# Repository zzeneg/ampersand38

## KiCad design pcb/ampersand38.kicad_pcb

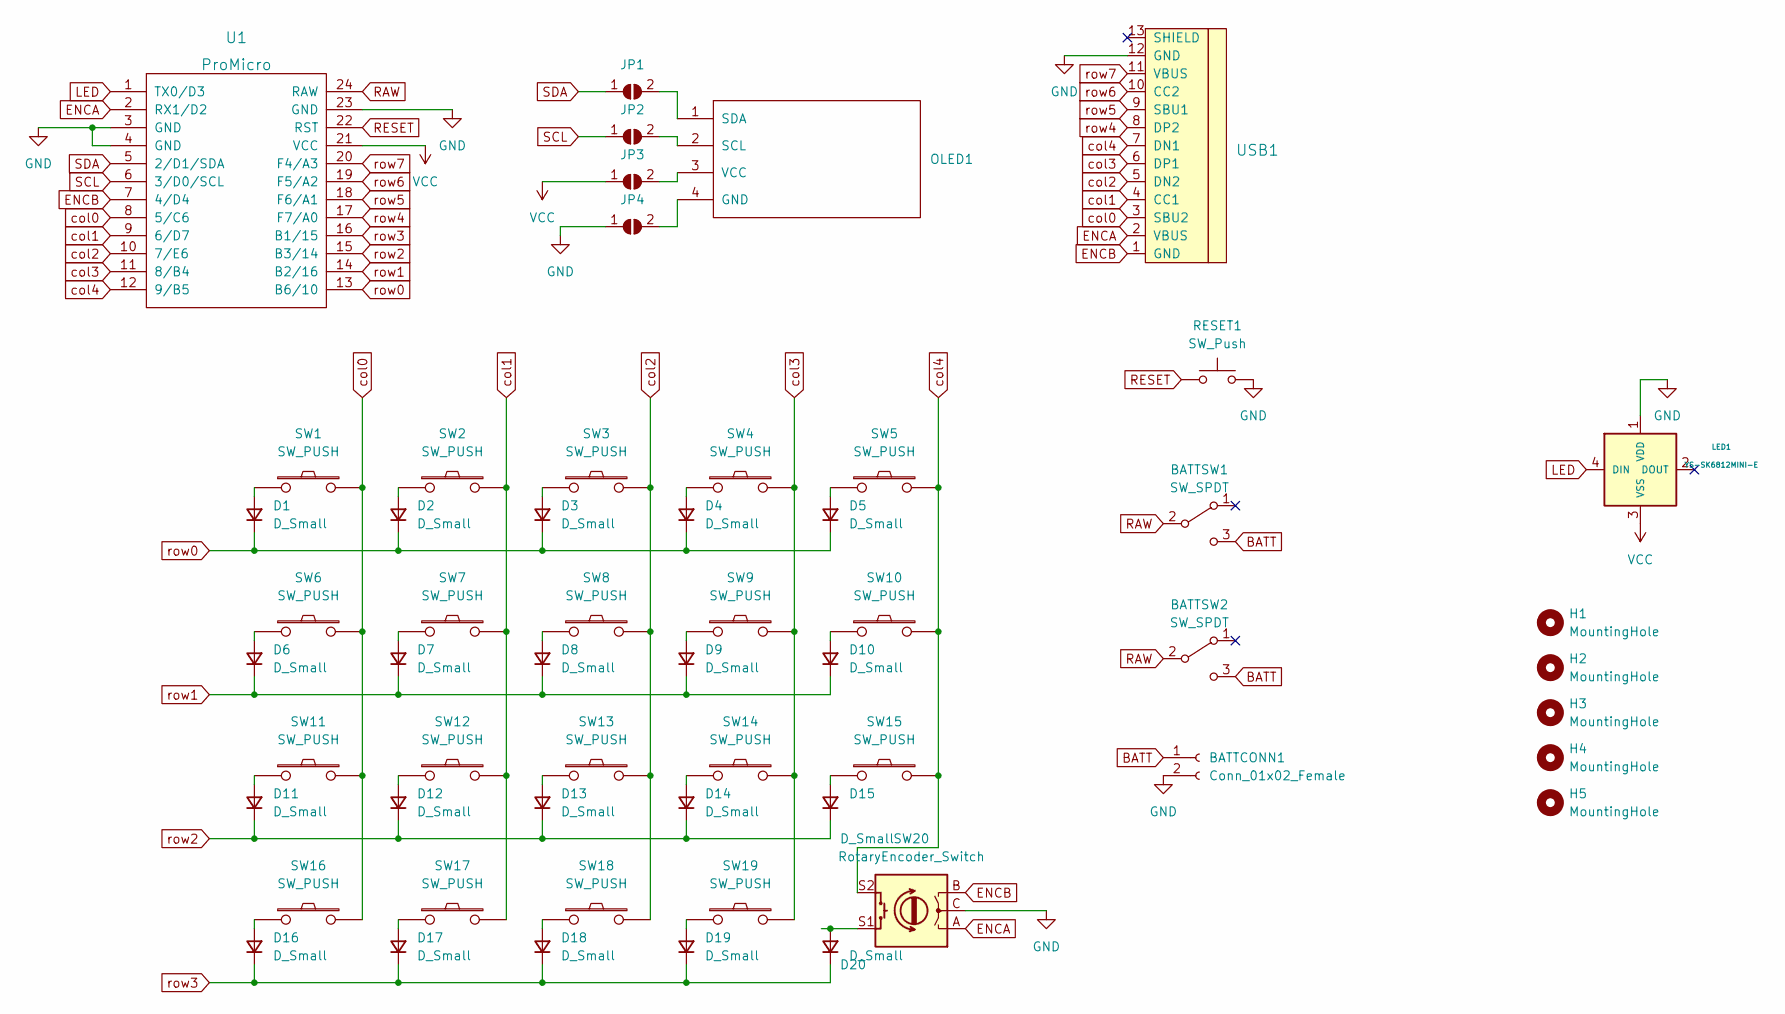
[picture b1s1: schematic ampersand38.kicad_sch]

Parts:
BATTCONN1: Conn_01x02_Female; JST_XH_S2B-XH-A_1x02_P2.50mm_Horizontal
BATTSW1, BATTSW2: SW_SPDT; SW_SPDT_PCM12
D1, D2, D3, D4, D5, D6, D7, D8, D9, D10, D11, D12, D13, D14, D15, D16, D17, D18, D19, D20: D_Small; D_SOD123
H1, H2, H3, H4, H5: MountingHole
JP1, JP2, JP3, JP4: SolderJumper_2_Open; SolderJumper-2_P1.3mm_Open_TrianglePad1.0x1.5mm
LED1: YS-SK6812MINI-E; SK6812-MINI-E
OLED1: OLED; OLED_v2
RESET1: SW_Push; ResetSW
SW1, SW2, SW3, SW4, SW5, SW6, SW7, SW8, SW9, SW10, SW11, SW12, SW13, SW14, SW15, SW16, SW17, SW18: SW_PUSH; CherryMX_Hotswap
SW19: SW_PUSH; CherryMX_Hotswap_1.5
SW20: RotaryEncoder_Switch; RotaryEncoder_EC11-no-legs
U1: ProMicro
USB1: HRO-TYPE-C-31-M-12

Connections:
BATT: BATTCONN1.1, BATTSW1.3 (C), BATTSW2.3 (C)
ENCA: SW20.A, U1.2 (RX1/D2), USB1.2 (VBUS)
ENCB: SW20.B, U1.7 (4/D4), USB1.1 (GND)
GND: BATTCONN1.2, JP4.1 (A), LED1.1 (VDD), RESET1.2, SW20.C, U1.3 (GND), U1.4 (GND), U1.23 (GND), USB1.12 (GND)
LED: LED1.4 (DIN), U1.1 (TX0/D3)
unnamed: D1.2 (A), SW1.1
unnamed: D2.2 (A), SW2.1
unnamed: D3.2 (A), SW3.1
unnamed: D4.2 (A), SW4.1
unnamed: D5.2 (A), SW5.1
unnamed: D6.2 (A), SW6.1
unnamed: D7.2 (A), SW7.1
unnamed: D8.2 (A), SW8.1
unnamed: D9.2 (A), SW9.1
unnamed: D10.2 (A), SW10.1
unnamed: D11.2 (A), SW11.1
unnamed: D12.2 (A), SW12.1
unnamed: D13.2 (A), SW13.1
unnamed: D14.2 (A), SW14.1
unnamed: D15.2 (A), SW15.1
unnamed: D16.2 (A), SW16.1
unnamed: D17.2 (A), SW17.1
unnamed: D18.2 (A), SW18.1
unnamed: D19.2 (A), SW19.1
unnamed: D20.2 (A), SW20.S1
unnamed: JP1.2 (B), OLED1.1 (SDA)
unnamed: JP2.2 (B), OLED1.2 (SCL)
unnamed: JP3.2 (B), OLED1.3 (VCC)
unnamed: JP4.2 (B), OLED1.4 (GND)
RAW: BATTSW1.2 (B), BATTSW2.2 (B), U1.24 (RAW)
RESET: RESET1.1, U1.22 (RST)
SCL: JP2.1 (A), U1.6 (3/D0/SCL)
SDA: JP1.1 (A), U1.5 (2/D1/SDA)
VCC: JP3.1 (A), LED1.3 (VSS), U1.21 (VCC)
col0: SW1.2, SW6.2, SW11.2, SW16.2, U1.8 (5/C6), USB1.3 (SBU2)
col1: SW2.2, SW7.2, SW12.2, SW17.2, U1.9 (6/D7), USB1.4 (CC1)
col2: SW3.2, SW8.2, SW13.2, SW18.2, U1.10 (7/E6), USB1.5 (DN2)
col3: SW4.2, SW9.2, SW14.2, SW19.2, U1.11 (8/B4), USB1.6 (DP1)
col4: SW5.2, SW10.2, SW15.2, SW20.S2, U1.12 (9/B5), USB1.7 (DN1)
row0: D1.1 (K), D2.1 (K), D3.1 (K), D4.1 (K), D5.1 (K), U1.13 (B6/10)
row1: D6.1 (K), D7.1 (K), D8.1 (K), D9.1 (K), D10.1 (K), U1.14 (B2/16)
row2: D11.1 (K), D12.1 (K), D13.1 (K), D14.1 (K), D15.1 (K), U1.15 (B3/14)
row3: D16.1 (K), D17.1 (K), D18.1 (K), D19.1 (K), D20.1 (K), U1.16 (B1/15)
row4: U1.17 (F7/A0), USB1.8 (DP2)
row5: U1.18 (F6/A1), USB1.9 (SBU1)
row6: U1.19 (F5/A2), USB1.10 (CC2)
row7: U1.20 (F4/A3), USB1.11 (VBUS)

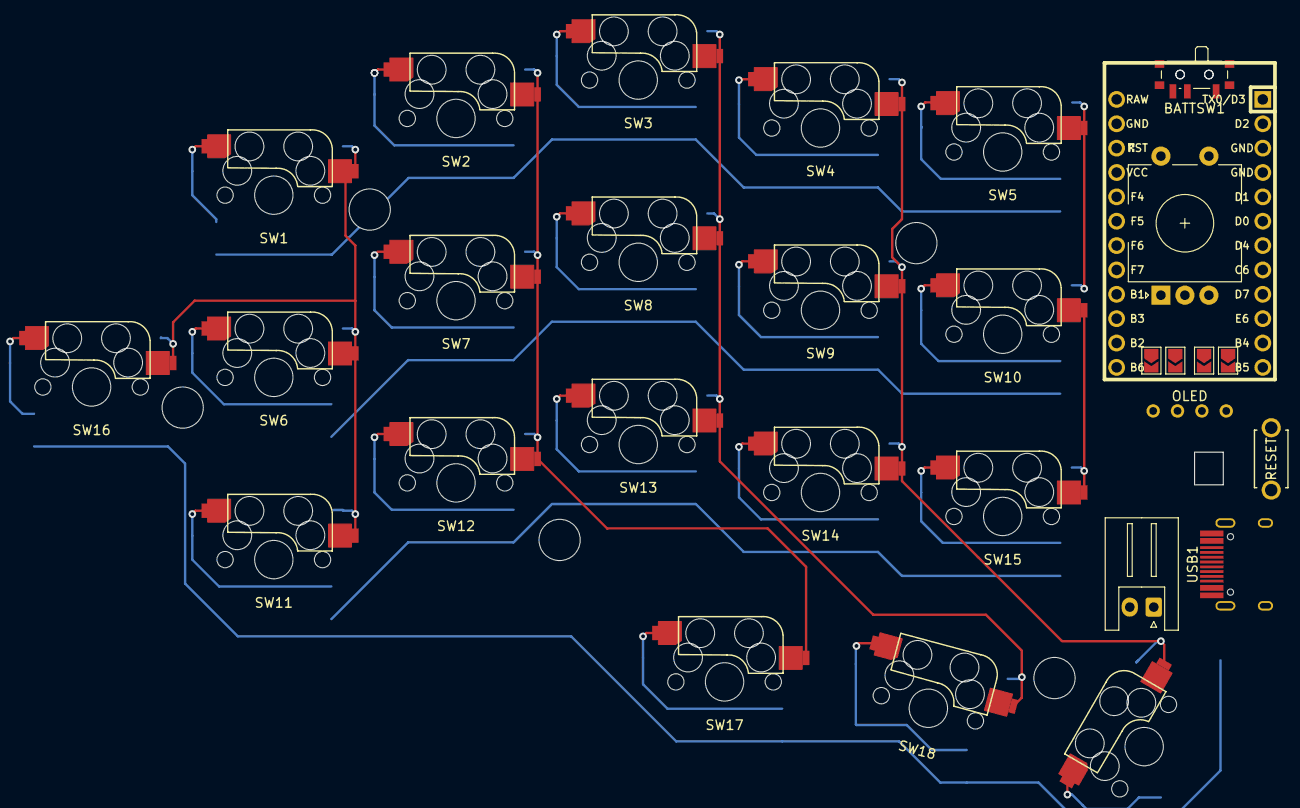
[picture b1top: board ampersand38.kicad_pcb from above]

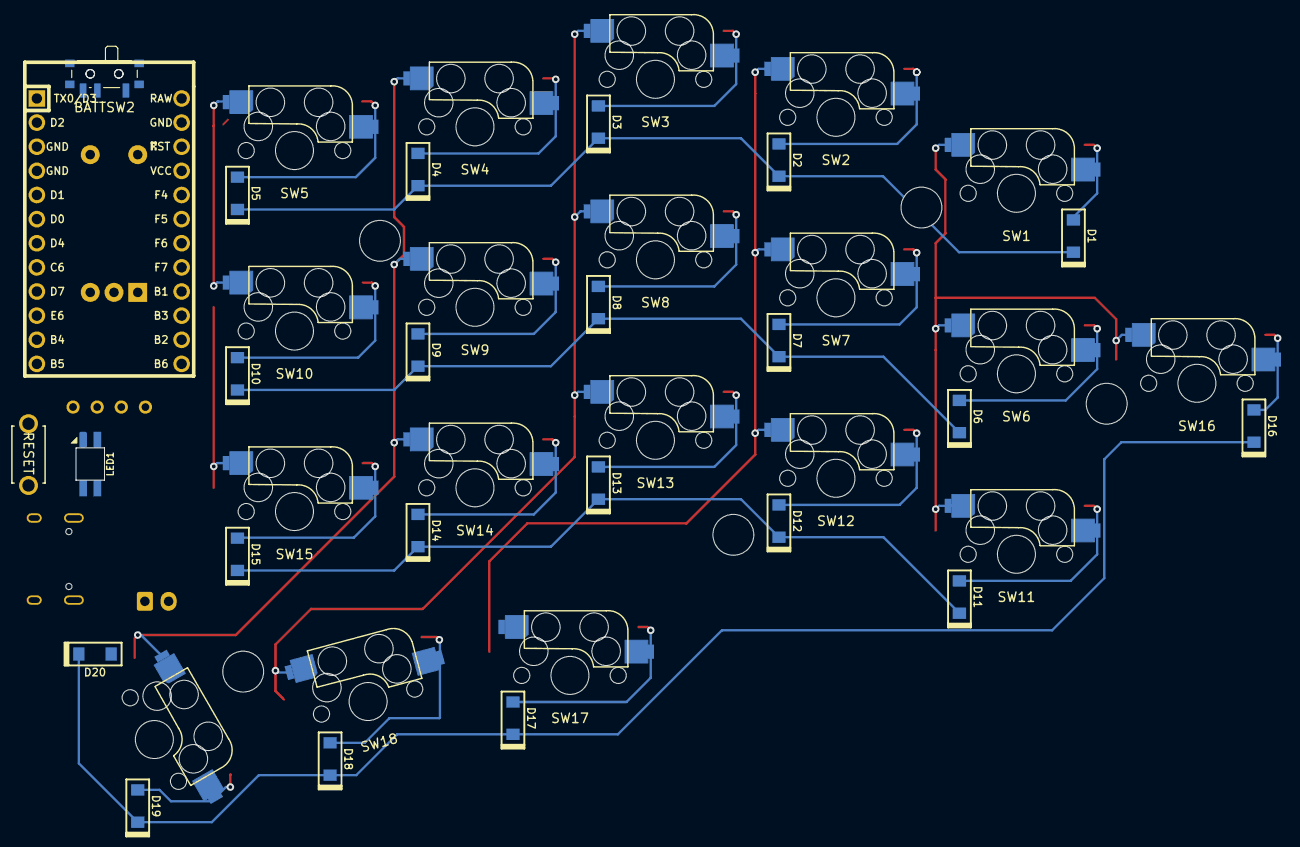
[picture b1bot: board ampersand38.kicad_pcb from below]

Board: 2 copper layers, 57 parts (23 on the bottom side), 47 nets.

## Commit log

2022-05-06 add libs
2022-05-10 unfinished
